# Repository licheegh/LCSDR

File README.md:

# LCSDR

more at <http://www.squirrel-electronics.com/lcsdrgong-cheng.html>

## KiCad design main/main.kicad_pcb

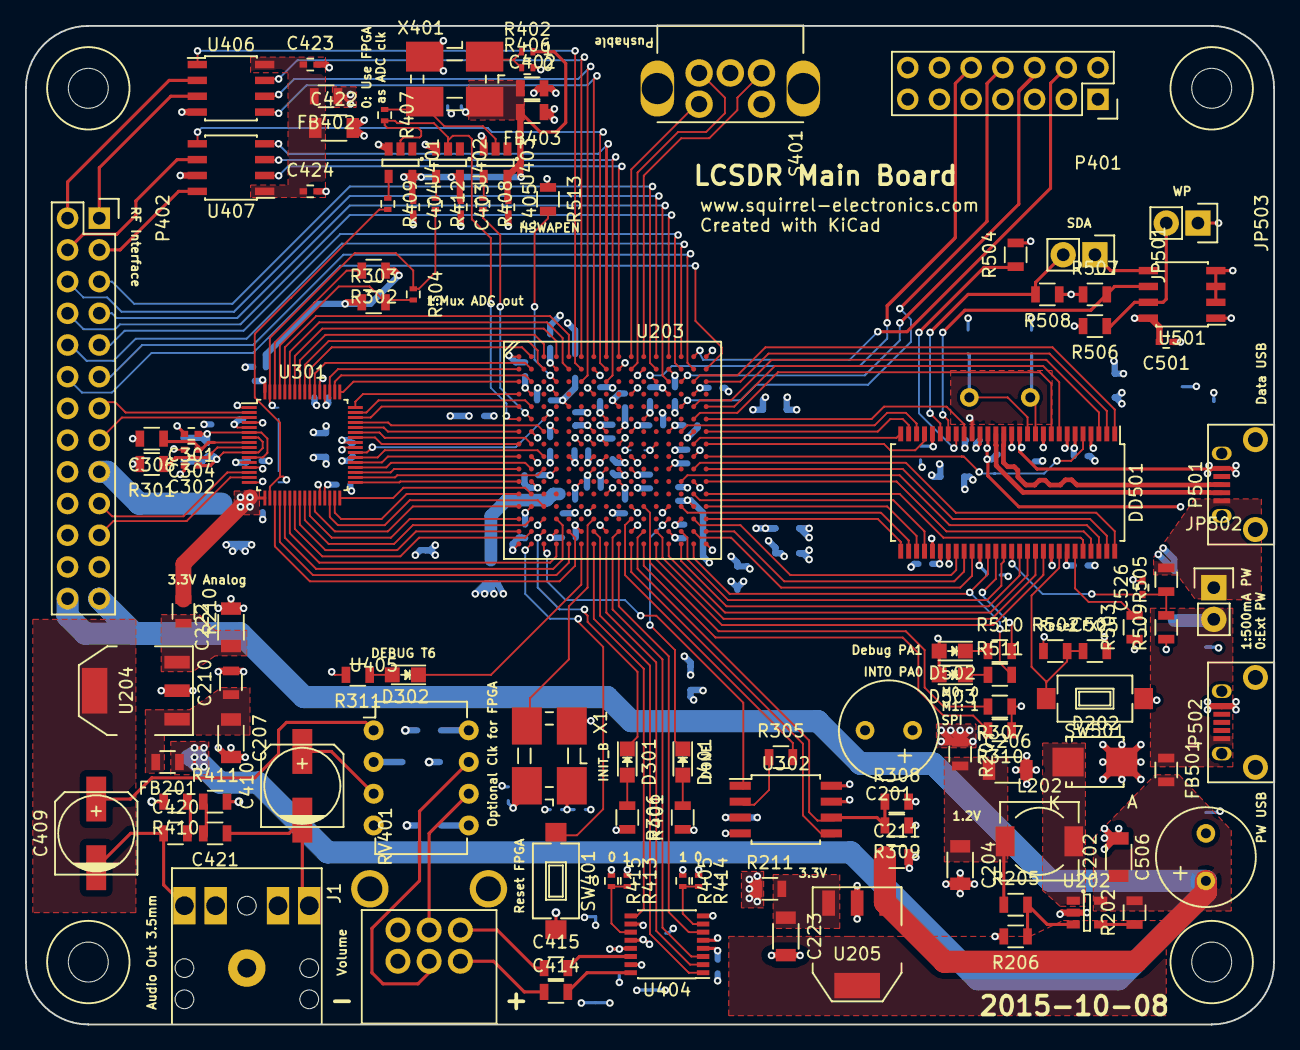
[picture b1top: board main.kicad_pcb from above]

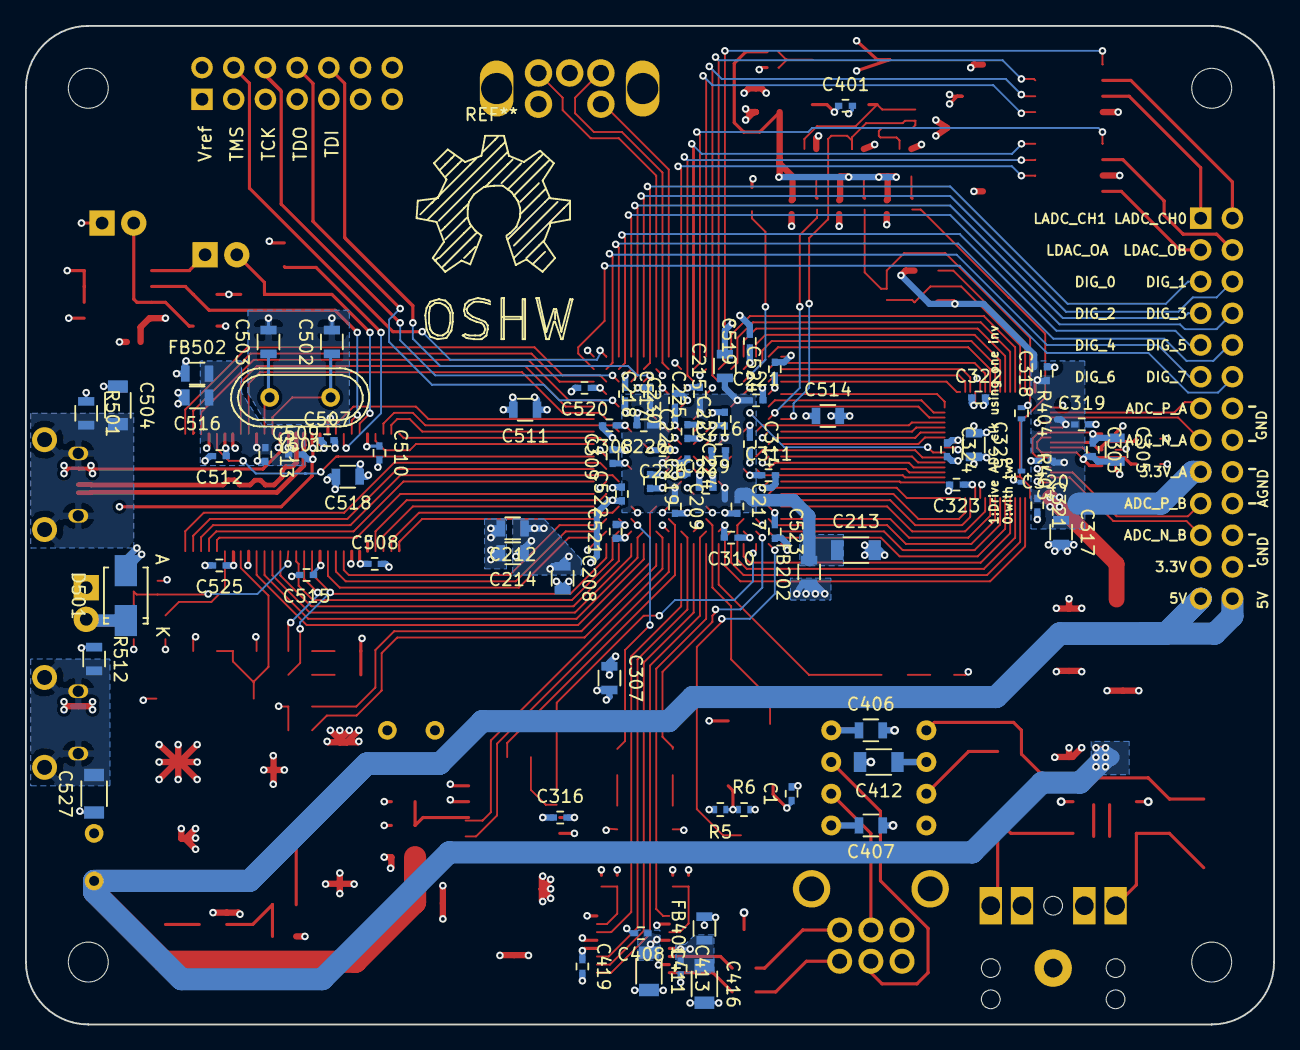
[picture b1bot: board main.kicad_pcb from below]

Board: 4 copper layers, 100.0 x 80.0 mm, 196 parts (81 on the bottom side), 187 nets.

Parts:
C1, C209, C216, C217, C218, C219, C220, C221, C224, C225, C226, C227, C228, C229, C230, C301, C302, C303, C304, C308, C309, C310, C311, C314, C316, C318, C319, C320, C321, C322, C323, C324, C401, C403, C404, C405, C408, C413, C419, C423, C424, C501, C507, C508, C509, C510, C512, C513, C515, C517, C519, C520, C521, C522, C523, C524, C525, C526: 0.47u; C_0402
C201, C506: 470u; Elko_vert_11.5x8mm_RM3.5
C202: 22U; C_1206
C204, C206, C207, C213, C222, C223, C411, C412, C416, C422: 22u; C_1206
C208, C210, C211, C212, C214, C215, C305, C306, C307, C317, C325, C402, C406, C407, C414, C415, C505, C511, C514, C516, C518: 4.7u; R_0805
C409, C410: 47u; c_elec_6.3x5.8
C420, C421: 0.1u; R_0805
C502, C503: 12p; R_0805
C504, C527: 4.7n 250V; C_1206
D202: D_Schottky; SMB_Standard
D301, D302, D401, D502, D503: LED; LED-0805
D501: TVS; SMA_Standard
DD501: IC_CY7C68013A; SSOP-56_7.5x18.5mm_Pitch0.635mm
FB201, FB202, FB501: FILTER; R_0805
FB401, FB402, FB403, FB502: FB; R_0805
J1: JACK_TRS_5PINS; 5PIN_3.5mm_Audio_Jack_Wide
JP501, JP502, JP503: JUMPER; Pin_Header_Straight_1x02
L202: INDUCTOR; Choke_SMD_6.3x6.3_H3
M401, M402, M403, M404: Mount_Hole; Mounting_Hole_3mm
P401: CONN_02X07; Socket_Strip_Straight_2x07
P402: CONN_02X13; Socket_Strip_Straight_2x13
P501, P502: USB_OTG; USB_Micro-B
R5, R6, R304, R402, R403, R404, R405, R406, R407, R408, R409, R412, R413, R414, R415: 0; R_0402
R202, R301, R302, R303, R502, R503, R506: 100k; R_0805
R205, R206, R504, R505: 10k; R_0805
R207, R210, R211: 0; R_0805
R305: 100; R_0805
R306, R311, R401, R510, R511, R513: 560; R_0805
R307, R308, R309, R310: 2.4k; R_0805
R410, R411: 4.7; R_0805
R501, R512: 1Meg; R_0805
R507, R508: 2.2k; R_0805
R509: 20k; R_0805
RV401: DUAL_POT_WITH_SHIELD; RK09L12
S401: Encoder_with_swith; EC11B15242A
SW401, SW501: SW_PUSH; SW_SPST_FSMSM
U202: LMR10515-SOT23; SOT-23-5
U203: XC6SLX25-FTG256; BGA-256_pitch1mm_dia0.4mm
U204, U205: General_SOT223_LDO; SOT-223
U301: AD92x8; LQFP-64_7x7mm_Pitch0.4mm
U302: 25_Serial_Flash_8_Pin; SOIJ-8_5.3x5.3mm_Pitch1.27mm
U401, U402, U403: 74AHC1G04; SOT-23-5
U404: UDA1334x; SSOP-16_4.4x5.2mm_Pitch0.65mm
U405: TDA2822M; DIP-8_W7.62mm
U406: MCP3202; SOIC-8_3.9x4.9mm_Pitch1.27mm
U407: MCP48x2; SOIC-8_3.9x4.9mm_Pitch1.27mm
U501: 24C16; SOIC-8_3.9x4.9mm_Pitch1.27mm
X1, X401: 4-Pin_Oscillator; oscillator_4Pin_5032_7050
Y501: Crystal; Crystal_HC49-U_Vertical

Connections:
+1V2: C201.1, C208.1, C212.1, C214.1, C216.1, C219.1, C224.1, C226.1, C227.1, C228.1, C229.1, C230.1, R207.1, U203.G7, U203.G9, U203.H8, U203.H10, U203.J7, U203.J9, U203.K8, U203.K10
+3.3VADC: C317.1, C318.1, C319.1, C320.1, C321.1, P402.17, R210.1, R302.1, R303.1, U301.5, U301.12, U301.17, U301.64
+3V3: C1.1, C307.1, C308.1, C309.1, C310.1, C311.1, C314.1, C316.2, C322.1, C323.1, C324.1, C325.1, C412.1, C419.1, C501.2, C507.1, C508.1, C510.1, C511.1, C512.1, C514.1, C515.1, C517.1, C518.1, C519.1, C520.1, C521.1, C522.1, C523.1, C524.1, C525.1, D502.2, D503.2, DD501.6, DD501.18, DD501.24, DD501.34, DD501.39, DD501.50, FB202.1, FB401.2, FB402.1, FB403.1, FB502.1, JP503.1, P401.2, P402.23, R5.2, R211.1, R306.2, R308.2, R311.2, R401.1, R405.1, R413.1, R502.1, R503.1, R507.1, R508.1, U203.B4, U203.B9, U203.B13, U203.D2, U203.D7, U203.D10, U203.D15, U203.G4, U203.G13, U203.J2, U203.J15, U203.K4, U203.K13, U203.N2, U203.N7, U203.N10, U203.N15, U203.R4, U203.R8, U203.R13, U301.29, U301.41, U301.52, U302.3, U302.7, U302.8, U404.4, U405.2, U501.1, U501.8, X1.4
+5V: C202.1, C211.1, C506.1, FB201.1, FB501.2, P402.25, P402.26, R202.2, U202.5, U205.1
/ADC/CLK: R308.1, R309.2, U203.R11, U302.6
/ADC/CS: U203.T3, U302.1
/ADC/DCS: U203.R5, U301.19
/ADC/DEBUG_LED: D302.1, U203.T6
/ADC/DFS: U203.T5, U301.20
/ADC/DI: U203.T10, U302.5
/ADC/DO: R305.2, U203.P10
/ADC/D_A0: U203.H1, U301.42
/ADC/D_A1: U203.H2, U301.43
/ADC/D_A2: U203.G1, U301.44
/ADC/D_A3: U203.G3, U301.45
/ADC/D_A4: U203.E1, U301.46
/ADC/D_A5: U203.E2, U301.47
/ADC/D_A6: U203.D1, U301.48
/ADC/D_A7: U203.C1, U301.49
/ADC/D_A8: U203.C2, U301.50
/ADC/D_A9: U203.B1, U301.51
/ADC/D_A10: U203.B2, U301.54
/ADC/D_A11: U203.A2, U301.55
/ADC/D_A12: U203.B3, U301.56
/ADC/D_A13: U203.A3, U301.57
/ADC/D_B0: U203.R2, U301.23
/ADC/D_B1: U203.R1, U301.24
/ADC/D_B2: U203.P2, U301.25
/ADC/D_B3: U203.P1, U301.26
/ADC/D_B4: U203.N1, U301.27
/ADC/D_B5: U203.N3, U301.30
/ADC/D_B6: U203.M1, U301.31
/ADC/D_B7: U203.M2, U301.32
/ADC/D_B8: U203.L1, U301.33
/ADC/D_B9: U203.K3, U301.34
/ADC/D_B10: U203.K1, U301.35
/ADC/D_B11: U203.K2, U301.36
/ADC/D_B12: U203.J1, U301.37
/ADC/D_B13: U203.J3, U301.38
/ADC/INIT_B: D301.1, U203.R3
/ADC/M0: R310.2, U203.T11
/ADC/M1: R307.2, U203.N11
/ADC/OEB_B: U203.T4, U301.22
/ADC/OTR_B: U203.F3, U301.39
/ADC/PDWN_B: U203.P4, U301.21
/PSU/VCCAUX: C209.1, C213.1, C215.1, C217.1, C218.1, C220.1, C221.1, C225.1, FB202.2, U203.E5, U203.F8, U203.F11, U203.G10, U203.H6, U203.J10, U203.L6, U203.L9
/USB/+3.3VFX2: C509.1, C513.1, C516.1, DD501.10, DD501.14, FB502.2
/USB/CLKO: DD501.5, U203.J16
/USB/D_N: DD501.16, P501.2
/USB/D_P: DD501.15, P501.3
/USB/FD0: DD501.25, U203.H16
/USB/FD1: DD501.26, U203.G14
/USB/FD2: DD501.27, U203.G16
/USB/FD3: DD501.28, U203.H15
/USB/FD4: DD501.29, U203.P16
/USB/FD5: DD501.30, U203.N14
/USB/FD6: DD501.31, U203.N16
/USB/FD7: DD501.32, U203.M15
/USB/FD8: DD501.52, U203.M16
/USB/FD9: DD501.53, U203.L16
/USB/FD10: DD501.54, U203.L14
/USB/FD11: DD501.55, U203.K16
/USB/FD12: DD501.56, U203.K15
/USB/FD13: DD501.1, U203.C15
/USB/FD14: DD501.2, U203.C16
/USB/FD15: DD501.3, U203.E15
/USB/FIFOADR0: DD501.44, U203.T14
/USB/FIFOADR1: DD501.45, U203.T13
/USB/FLAGA: DD501.36, U203.P15
/USB/FLAGB: DD501.37, U203.R16
/USB/FLAGC: DD501.38, U203.R15
/USB/FX2_LED: DD501.41, R510.2
/USB/IFCLK: DD501.20, U203.F16
/USB/INT0: DD501.40, R511.2, U203.T15
/USB/PKTEND: DD501.46, U203.R12
/USB/SCL: DD501.22, R507.2, U501.6
/USB/SDA: DD501.23, JP501.2, R508.2
/USB/SLCS: DD501.47, U203.T12
/USB/SLOE: DD501.42, U203.R14
/USB/SLRD: DD501.8, U203.E16
/USB/SLWR: DD501.9, U203.F15
/USB/VBUS_DET: JP502.1, P501.1, R505.2
/USB/VBUS_DET_3V3: C526.1, DD501.43, R505.1, R509.2
/USB/XTAL_IN: C502.1, DD501.12, Y501.1
/USB/XTAL_OUT: C503.1, DD501.11, Y501.2
/USB/unfil_5V: D501.1, FB501.1, JP502.2, P502.1
/etc/3V3_LANA: C422.1, C423.1, C424.1, FB402.2, U406.8, U407.1
/etc/LADC_CH0: P402.2, U406.2
/etc/LADC_CH1: P402.1, U406.3
/etc/LDAC_OA: P402.3, U407.8
/etc/LDAC_OB: P402.4, U407.6
/etc/L_OUT: C415.1, RV401.6
/etc/R_OUT: C414.1, RV401.3
/etc/TCK: P401.6, U203.C14
/etc/TDI: P401.10, U203.C12
/etc/TDO: P401.8, U203.E14
/etc/TMS: P401.4, U203.A15
/etc/VCLK: C401.1, C402.1, C403.1, C404.1, C405.1, FB403.2, R402.2, U401.5, U402.5, U403.5, X401.4
ADC_CLK_A: R304.1, R404.1, R412.2, U301.63
ADC_CLK_B: R403.2, R409.2, U301.18
ADC_CLK_FPGA: R408.2, U203.F2
ADC_OEB_A: U203.B5, U301.59
ADC_OTR_A: U203.A4, U301.58
ADC_PWDN_A: U203.A5, U301.60
ADC_VIN_N_A: P402.15, U301.3
ADC_VIN_N_B: P402.19, U301.14
ADC_VIN_P_A: P402.13, U301.2
ADC_VIN_P_B: P402.21, U301.15
DAC_BCK: U203.R7, U404.1
DAC_DATAI: U203.R9, U404.3
DAC_DEEM: U203.T7, U404.9
DAC_PLL: U203.T9, U404.6
DAC_WS: U203.T8, U404.2
FPGA_CLKIN: U203.P7, X1.3
FPGA_CLKOUT_ADC: R407.2, U203.F1, U401.2, U402.2
FPGA_ENC_A: S401.A, U203.A11
FPGA_ENC_B: S401.B, U203.B10
FPGA_ENC_SW: S401.E, U203.A10
FPGA_RF_0: P402.5, U203.B12
FPGA_RF_1: P402.6, U203.A12
FPGA_RF_2: P402.7, U203.C13
FPGA_RF_3: P402.8, U203.A13
FPGA_RF_4: P402.9, U203.B14
FPGA_RF_5: P402.10, U203.A14
FPGA_RF_6: P402.11, U203.B15
FPGA_RF_7: P402.12, U203.B16
GND: C1.2, C201.2, C202.2, C204.2, C206.2, C207.2, C208.2, C209.2, C210.2, C211.2, C212.2, C213.2, C214.2, C215.2, C216.2, C217.2, C218.2, C219.2, C220.2, C221.2, C222.2, C223.2, C224.2, C225.2, C226.2, C227.2, C228.2, C229.2, C230.2, C301.2, C302.2, C304.2, C306.2, C307.2, C308.2, C309.2, C310.2, C311.2, C314.2, C316.1, C317.2, C318.2, C319.2, C320.2, C321.2, C322.2, C323.2, C324.2, C325.2, C401.2, C402.2, C403.2, C404.2, C405.2, C406.2, C407.1, C408.2, C411.2, C412.2, C413.2, C416.2, C419.2, C422.2, C423.2, C424.2, C501.1, C502.2, C503.2, C504.1, C505.2, C506.2, C507.2, C508.2, C509.2, C510.2, C511.2, C512.2, C513.2, C514.2, C515.2, C516.2, C517.2, C518.2, C519.2, C520.2, C521.2, C522.2, C523.2, C524.2, C525.2, C526.2, C527.1, D202.2, D501.2, DD501.4, DD501.7, DD501.13, DD501.17, DD501.19, DD501.33, DD501.35, DD501.48, J1.1, P401.1, P401.3, P401.5, P401.7, P401.9, P401.11, P401.13, P402.14, P402.16, P402.18, P402.20, P402.22, P402.24, P501.5, P502.5, R6.2, R206.2, R301.2, R307.1, R309.1, R310.1, R406.2, R410.2, R411.2, R414.1, R415.1, R501.1, R504.2, R506.2, R509.1, R512.1, R513.1, RV401.1, RV401.4, RV401.7, S401.1, S401.C, S401.D, SW401.2, SW501.1, U202.2, U203.A1, U203.A16, U203.B7, U203.B11, U203.D4, U203.D13, U203.E9, U203.G2, U203.G8, U203.G15, U203.H7, U203.H9, U203.H12, U203.J5, U203.J8, U203.K7, U203.K9, U203.L2, U203.L15, U203.M8, U203.N13, U203.P3, U203.P14, U203.R6, U203.R10, U203.T1, U203.T16, U204.2, U205.2, U301.1, U301.4, U301.13, U301.16, U301.28, U301.40, U301.53, U302.4, U401.3, U402.3, U403.3, U404.5, U404.8, U404.10, U404.15, U405.4, U406.4, U407.7, U501.2, U501.3, U501.4, X1.2, X401.2
LADC_CLK: U203.A6, U406.7
LADC_CS: U203.B6, U406.1
LADC_DI: U203.A7, U406.5
LADC_DO: U203.C6, U406.6
LDAC_CLK: U203.C8, U407.3
LDAC_CS: U203.A9, U407.2
LDAC_DI: U203.A8, U407.4
LDAC_LD: U203.B8, U407.5
unnamed: C204.1, C206.1, L202.1, R205.1, R207.2
unnamed: C207.1, C210.1, FB201.2, U204.1
unnamed: C222.1, R210.2, U204.3
unnamed: C223.1, R211.2, U205.3
unnamed: C301.1, C303.1, C305.1, U301.6, U301.11
unnamed: C302.1, C303.2, C305.2, U301.7, U301.10
unnamed: C304.1, C306.1, U301.8
unnamed: C406.1, U405.8
unnamed: C407.2, U405.5
unnamed: C408.1, C411.1, U404.12
unnamed: C409.1, U405.1
unnamed: C409.2, C420.1, J1.2
unnamed: C410.1, U405.3
unnamed: C410.2, C421.1, J1.5
unnamed: C413.1, C416.1, FB401.1, U404.13
unnamed: C414.2, U404.16
unnamed: C415.2, U404.14
unnamed: C420.2, R410.1
unnamed: C421.2, R411.1
unnamed: C504.2, P501.6, R501.2
unnamed: C505.1, DD501.49, R502.2, SW501.2
unnamed: C527.2, P502.6, R512.2
unnamed: D202.1, L202.2, U202.1
unnamed: D301.2, R306.1
unnamed: D302.2, R311.1
unnamed: D401.1, U203.P13
unnamed: D401.2, R401.2
unnamed: D502.1, R510.1
unnamed: D503.1, R511.1
unnamed: DD501.21, R504.1
unnamed: DD501.51, R503.2
unnamed: JP501.1, U501.5
unnamed: JP503.2, R506.1, U501.7
unnamed: R5.1, R6.1, X1.1
unnamed: R202.1, U202.4
unnamed: R205.2, R206.1, U202.3
unnamed: R301.1, U301.9
unnamed: R302.2, U301.62
unnamed: R303.2, R304.2, U301.61
unnamed: R305.1, U302.2
unnamed: R402.1, R406.1, X401.1
unnamed: R403.1, R404.2
unnamed: R405.2, R414.2, U404.7
unnamed: R407.1, U403.2, X401.3
unnamed: R408.1, U403.4
unnamed: R409.1, U401.4
unnamed: R412.1, U402.4
unnamed: R413.2, R415.2, U404.11
unnamed: R513.2, U203.C4
unnamed: RV401.2, U405.7
unnamed: RV401.5, U405.6
unnamed: SW401.1, U203.T2

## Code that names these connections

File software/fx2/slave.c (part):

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BOOL done_frm_fpga = 0;

// EZUSB FX2 PORTA = slave fifo enable(s), when IFCFG[1:0]=11
//sbit PA0 = IOA ^ 0;             // alt. func., INT0#
//sbit PA1 = IOA ^ 1;             // alt. func., INT1#
// sbit PA2 = IOA ^ 2;          // is SLOE
//sbit PA3 = IOA ^ 3;             // alt. func., WU2
// sbit PA4 = IOA ^ 4;          // is FIFOADR0
// sbit PA5 = IOA ^ 5;          // is FIFOADR1
// sbit PA6 = IOA ^ 6;          // is PKTEND
// sbit PA7 = IOA ^ 7;          // is FLAGD

// EZUSB FX2 PORTC i/o...       port NA for 56-pin FX2
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
  //FF: Full, EF: Empty, PF: Program
  //00:EP2 10:EP6 EPs are used.
  PINFLAGSAB = 0xE8;			// FLAGA 8 - EP2EF, FLAGB E - EP6FF
  SYNCDELAY;
  PINFLAGSCD = 0x00;			// address selected.
  SYNCDELAY;
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
  // IFCLKSRC=1   , FIFOs executes on internal clk source 
  // xMHz=1       , 48MHz operation
  // IFCLKOE=1    ,Drive IFCLK pin signal at 48MHz
  // IFCLKPOL=0   , Don't invert IFCLK pin signal from internal clk
  // ASYNC=0      , master samples synchronous
  // GSTATE=0     , Don't drive GPIF states out on PORTE[2:0], debug WF
  // IFCFG[1:0]=11, FX2 in slave FIFO mode
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
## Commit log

2015-11-01 to public
2018-01-17 add software things.
    It is not release ready yet.But people can reference to it.

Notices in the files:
software/fx2/slave.c:
Copyright (c) 2003 Cypress Semiconductor All rights reserved
